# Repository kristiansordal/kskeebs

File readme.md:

# kskeebs
This repo contains PCB designs and CAD files for a 36-key split keyboard I'm currently designing. Still very WIP.

## Pictures

### PCB Design

### 3D Model

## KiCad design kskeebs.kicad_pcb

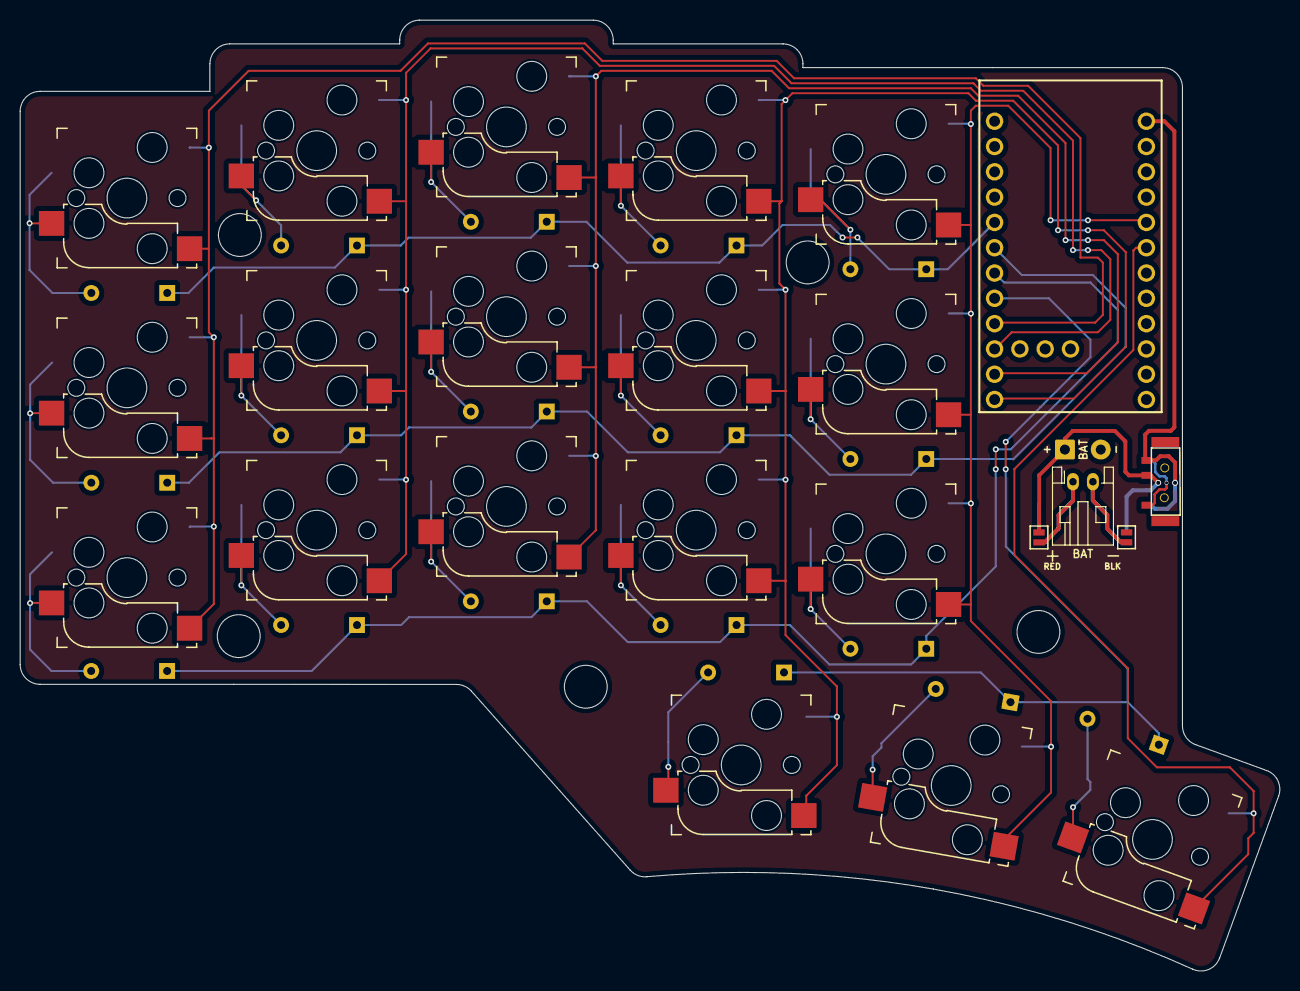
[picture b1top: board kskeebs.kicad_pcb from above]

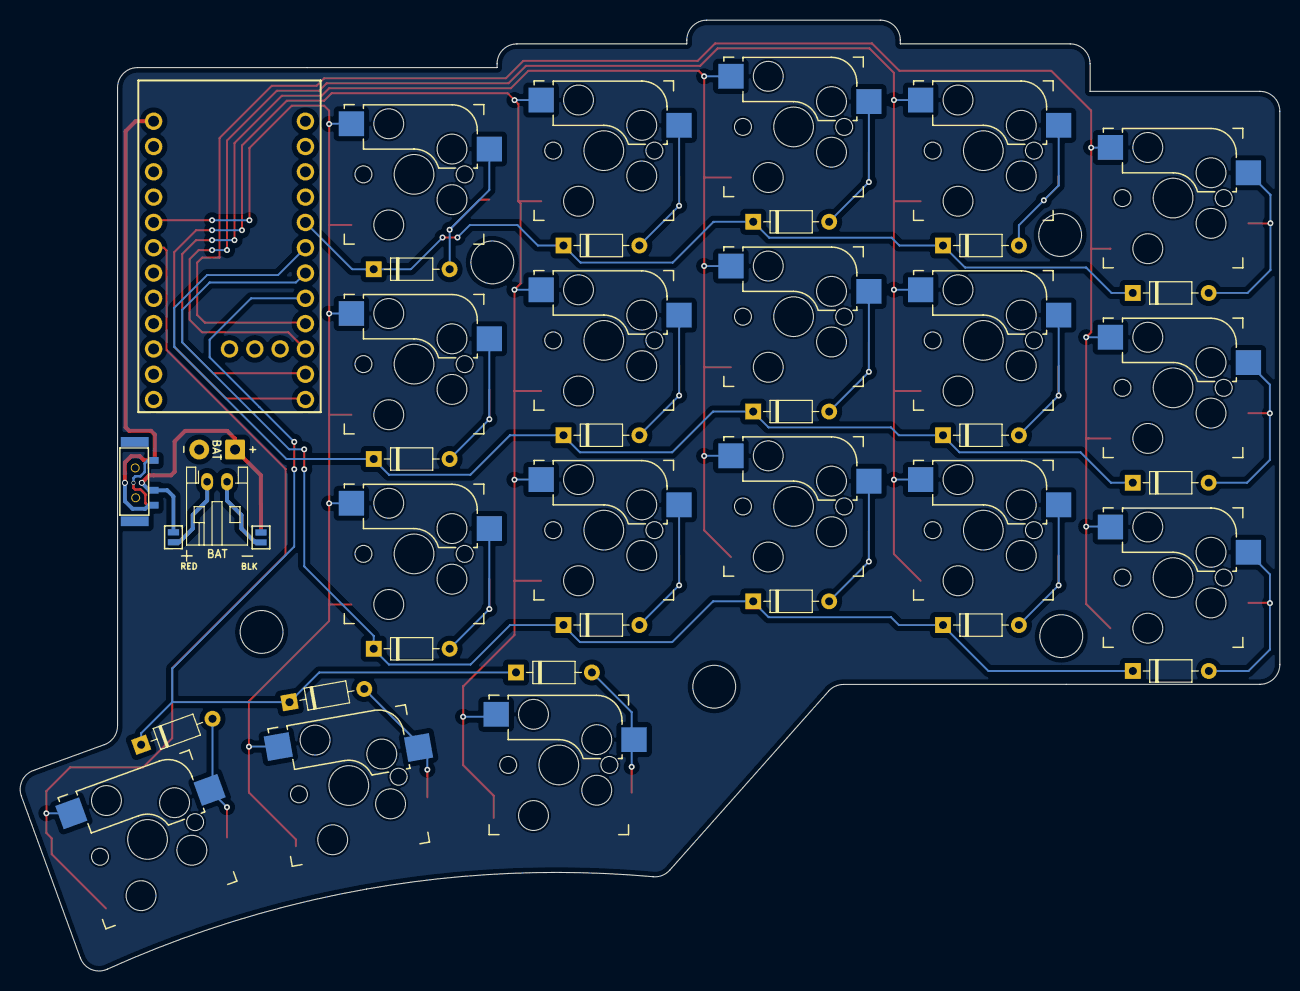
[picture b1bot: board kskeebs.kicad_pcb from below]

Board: 2 copper layers, 126.5 x 95.5 mm, 44 parts (20 on the bottom side), 32 nets.

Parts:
BT1: JST Connector; JST_PH_reversible
BT1#2: Battery_Cell; custombatteryconnector_small
D1, D2, D3, D4, D5, D6, D7, D8, D9, D10, D11, D12, D13, D14, D15, D16, D17, D18: Diode; Diode_DO-35
JP1, JP2, JP3, JP4: Device_Jumper_NO_Small; Jumper
PSW1: SW_SPDT; MSK12C02_reversible
S1, S2, S3, S4, S5, S6, S7, S8, S9, S10, S11, S12, S13, S14, S15, S16, S17, S18: Keyswitch; Kailh_socket_MX_reversible
U1: Nice_Nano_V2

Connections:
/PAD1: JP3.1, JP4.1
/PAD2: JP1.1, JP2.1
/PSW: BT1#2.1 (+), JP1.2, JP4.2
Col 0: S1.1, S6.1, S11.1, U1.9 (6)
Col 1: S2.1, S7.1, S12.1, U1.10 (7)
Col 2: S3.1, S8.1, S13.1, U1.11 (8)
Col 3: S4.1, S9.1, S14.1, S16.1, U1.12 (9)
Col 4: S5.1, S10.1, S15.1, S17.1, U1.20 (21)
Col 5: S18.1, U1.19 (20)
GND: BT1#2.2 (-), JP2.2, JP3.2
unnamed: D1.2 (A), S1.2
unnamed: D2.2 (A), S2.2
unnamed: D3.2 (A), S3.2
unnamed: D4.2 (A), S4.2
unnamed: D5.2 (A), S5.2
unnamed: D6.2 (A), S6.2
unnamed: D7.2 (A), S7.2
unnamed: D8.2 (A), S8.2
unnamed: D9.2 (A), S9.2
unnamed: D10.2 (A), S10.2
unnamed: D11.2 (A), S11.2
unnamed: D12.2 (A), S12.2
unnamed: D13.2 (A), S13.2
unnamed: D14.2 (A), S14.2
unnamed: D15.2 (A), S15.2
unnamed: D16.2 (A), S16.2
unnamed: D17.2 (A), S17.2
unnamed: D18.2 (A), S18.2
Row 0: D1.1 (K), D2.1 (K), D3.1 (K), D4.1 (K), D5.1 (K), U1.5 (2)
Row 1: D6.1 (K), D7.1 (K), D8.1 (K), D9.1 (K), D10.1 (K), U1.6 (3)
Row 2: D11.1 (K), D12.1 (K), D13.1 (K), D14.1 (K), D15.1 (K), U1.7 (4)
Row 3: D16.1 (K), D17.1 (K), D18.1 (K), U1.8 (5)

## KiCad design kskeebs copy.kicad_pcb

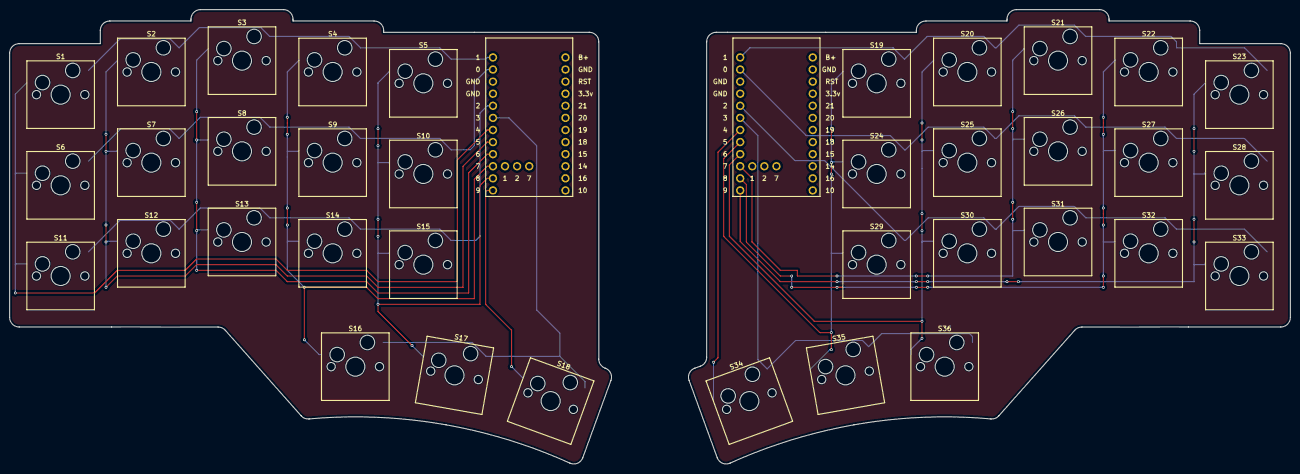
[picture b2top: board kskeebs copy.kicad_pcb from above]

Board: 2 copper layers, 269.1 x 95.5 mm, 38 parts (0 on the bottom side), 20 nets.

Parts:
S1, S2, S3, S4, S5, S6, S7, S8, S9, S10, S11, S12, S13, S14, S15, S16, S17, S18, S19, S20, S21, S22, S23, S24, S25, S26, S27, S28, S29, S30, S31, S32, S33, S34, S35, S36: Keyswitch; Hotswap_MX_1.00u
U1, U2: Nice_Nano_V2

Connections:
Col 0: S1.1, S6.1, S11.1, U1.7 (4)
Col 1: S2.1, S7.1, S12.1, U1.8 (5)
Col 2: S3.1, S8.1, S13.1, U1.9 (6)
Col 3: S4.1, S9.1, S14.1, S16.1, U1.10 (7)
Col 4: S5.1, S10.1, S15.1, S17.1, U1.11 (8)
Col 5: S18.1, U1.12 (9)
Col 6: S34.1, U2.7 (4)
Col 7: S19.1, S24.1, S29.1, S35.1, U2.8 (5)
Col 8: S20.1, S25.1, S30.1, S36.1, U2.9 (6)
Col 9: S21.1, S26.1, S31.1, U2.10 (7)
Col 10: S22.1, S27.1, S32.1, U2.11 (8)
Col 11: S23.1, S28.1, S33.1, U2.12 (9)
Row 0: S1.2, S2.2, S3.2, S4.2, S5.2, U1.1
Row 1: S6.2, S7.2, S8.2, S9.2, S10.2, U1.2 (0)
Row 2: S11.2, S12.2, S13.2, S14.2, S15.2, U1.5 (2)
Row 3: S16.2, S17.2, S18.2, U1.6 (3)
Row 4: S19.2, S20.2, S21.2, S22.2, S23.2, U2.1
Row 5: S24.2, S25.2, S26.2, S27.2, S28.2, U2.2 (0)
Row 6: S29.2, S30.2, S31.2, S32.2, S33.2, U2.5 (2)
Row 7: S34.2, S35.2, S36.2, U2.6 (3)

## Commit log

2024-04-23 init
2024-04-23 asdf
